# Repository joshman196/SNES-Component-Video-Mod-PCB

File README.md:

# SNES Component Video Mod PCB

A PCB that carries Pb and Pr video lines with their respective components. The Y line is not on the PCB as we will just wire it directly from the multi-out port instead. This mod does not work on stock SNES Jr. or "1-Chip" consoles. Compatible stock consoles **must** contain an S-ENC chip. Sometimes the S-ENC chip is alternatively labelled as "BA6594AF" or may be a revision labelled as "S-ENC A" or "S-ENC B."

## Parts Needed

- 2x 220uF 6.3v Capacitors [Digikey Part](https://www.digikey.com/en/products/detail/panasonic-electronic-components/ECE-A0JKA221/44725)
- 2x 75 Ohm Resistors [Digikey Part](https://www.digikey.com/en/products/detail/stackpole-electronics-inc/RNF14FTD75R0/1682415)
- 2x SS8050 Transistors [Digikey Part](https://www.digikey.com/en/products/detail/onsemi/SS8050DBU/1047260)
- 2x 1N4148 Diodes [Digikey Part](https://www.digikey.com/en/products/detail/onsemi/1N4148TR/458811)
- 3x RCA Jacks (preferrably color coded to YPbPr connections) **OR** 1x 3.5mm TRRS (4-pole) female connector with 1x 3.5mm TRRS to YPbPr adapter

For RCA jacks, you only really need 3 just to do the mod since those will carry the video output and you can use the multi-out port for the audio, but you can choose to get 5 RCA jacks instead so you can also do Left and Right Audio alongside the YPbPr jacks if you prefer. This guide does not cover the installation of audio RCA jacks.

For the TRRS jack method, it's generally considered best to desolder and remove the RF modulator from the console and put the TRRS jack in its place. If you don't want to remove the RF modulator, you will have to come up with a spot to put the TRRS jack, like drilling a hole into the shell for it. Also, you can figure out which pin on the back of the jack corresponds to which YPbPr female connector by checking continuity with a multimeter with the adapter plugged into the TRRS jack. Touch one lead of the multimeter to a pin on the back of the jack and the other lead to the inside of one of the connectors to figure out which one is which. One pin on the back of the TRRS jack may be longer than the others. This one should be the Ground pin.

## Install Guide

0. Turn off and unplug your console and open it by using a 4.5mm "Gamebit" screwdriver on the 6 screws on the bottom of the console.
1. Solder the parts to the mod PCB and find a suitable place inside your console to put the assembled board at so you can get a general idea of how long you want your wires to be. You may want to stick a layer of kapton tape covering the entire bottom side of the PCB or on the area of the main console board where you plan on setting the PCB down at. You may also choose to set the PCB somewhere off of the main board.
2. Connect a wire from pin 7 on the back or bottom of the multi-out connector to either your "Y" RCA jack (the green one) or the "Y" pin of your 3.5mm 4-pole (TRRS) to YPbPr adapter.
3. Connect a wire from pin 1 on the S-ENC chip to "Pr In" on the PCB.
4. Connect a wire from a 5V source on the main board to "+5V" on the PCB.
5. Connect a wire from pin 24 on the S-ENC chip to "Pb In" on the PCB.
6. Connect a wire from "Pr Out" on the PCB to either your "Pr" RCA jack (the red one) or the "Pr" pin of the TRRS YPbPr adapter.
7. Connect a wire from "Pb Out" on the PCB to either your "Pb" RCA jack (the blue one) or the "Pb" pin of the TRRS YPbPr adapter.
8. Connect a wire from "GND" on the PCB to a source of Ground on the SNES motherboard. There are some exposed ground planes near the 4 corners of the motherboard that you could use.

## Credits (2.x)

### Original Circuit Design:
- KPackLabs

## Credits (1.x)

### Original Circuit Design:
- NightWolve (Nicholas Livaditis)

### Other Credits:
- thesteve
- Duo_R
- Michael Moffitt

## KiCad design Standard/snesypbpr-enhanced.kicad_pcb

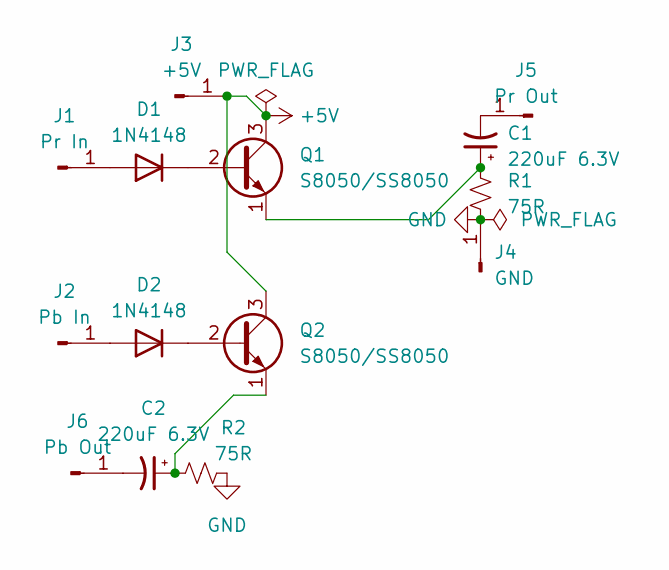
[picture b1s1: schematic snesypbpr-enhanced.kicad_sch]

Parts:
C1, C2: 220uF 6.3V; CP_Radial_D6.3mm_P2.50mm
D1, D2: 1N4148; D_DO-35_SOD27_P7.62mm_Horizontal
J1: Pr In; SolderWirePad_1x01_SMD_2x4mm
J2: Pb In; SolderWirePad_1x01_SMD_2x4mm
J3: +5V; SolderWirePad_1x01_SMD_2x4mm
J4: GND; SolderWirePad_1x01_SMD_2x4mm
J5: Pr Out; SolderWirePad_1x01_SMD_2x4mm
J6: Pb Out; SolderWirePad_1x01_SMD_2x4mm
Q1, Q2: S8050/SS8050; TO-92_Inline_Wide
R1, R2: 75R; R_Axial_DIN0207_L6.3mm_D2.5mm_P7.62mm_Horizontal

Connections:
+5V: J3.1, Q1.3 (C), Q2.3 (C)
GND: J4.1, R1.2, R2.2
unnamed: D1.2 (A), J1.1
unnamed: D1.1 (K), Q1.2 (B)
unnamed: D2.2 (A), J2.1
unnamed: D2.1 (K), Q2.2 (B)
unnamed: C1.2, J5.1
unnamed: C2.2, J6.1
unnamed: C1.1, Q1.1 (E), R1.1
unnamed: C2.1, Q2.1 (E), R2.1

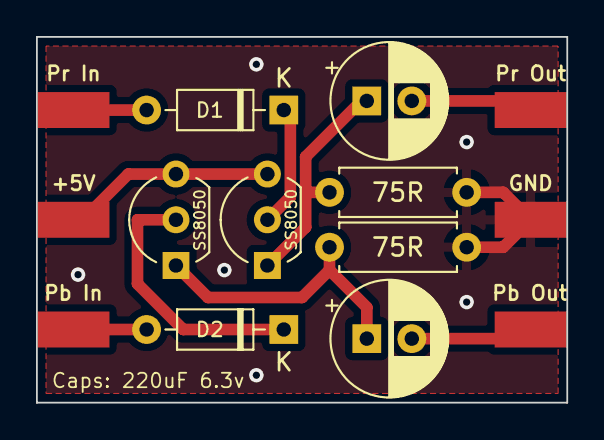
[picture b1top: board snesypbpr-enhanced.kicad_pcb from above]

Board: 2 copper layers, 29.5 x 20.3 mm, 14 parts (0 on the bottom side), 10 nets.

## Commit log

2023-08-20 initial file upload
